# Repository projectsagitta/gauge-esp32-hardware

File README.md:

# sagitta-shield
Oceanographic measuring shield for TTGO T-Energy.

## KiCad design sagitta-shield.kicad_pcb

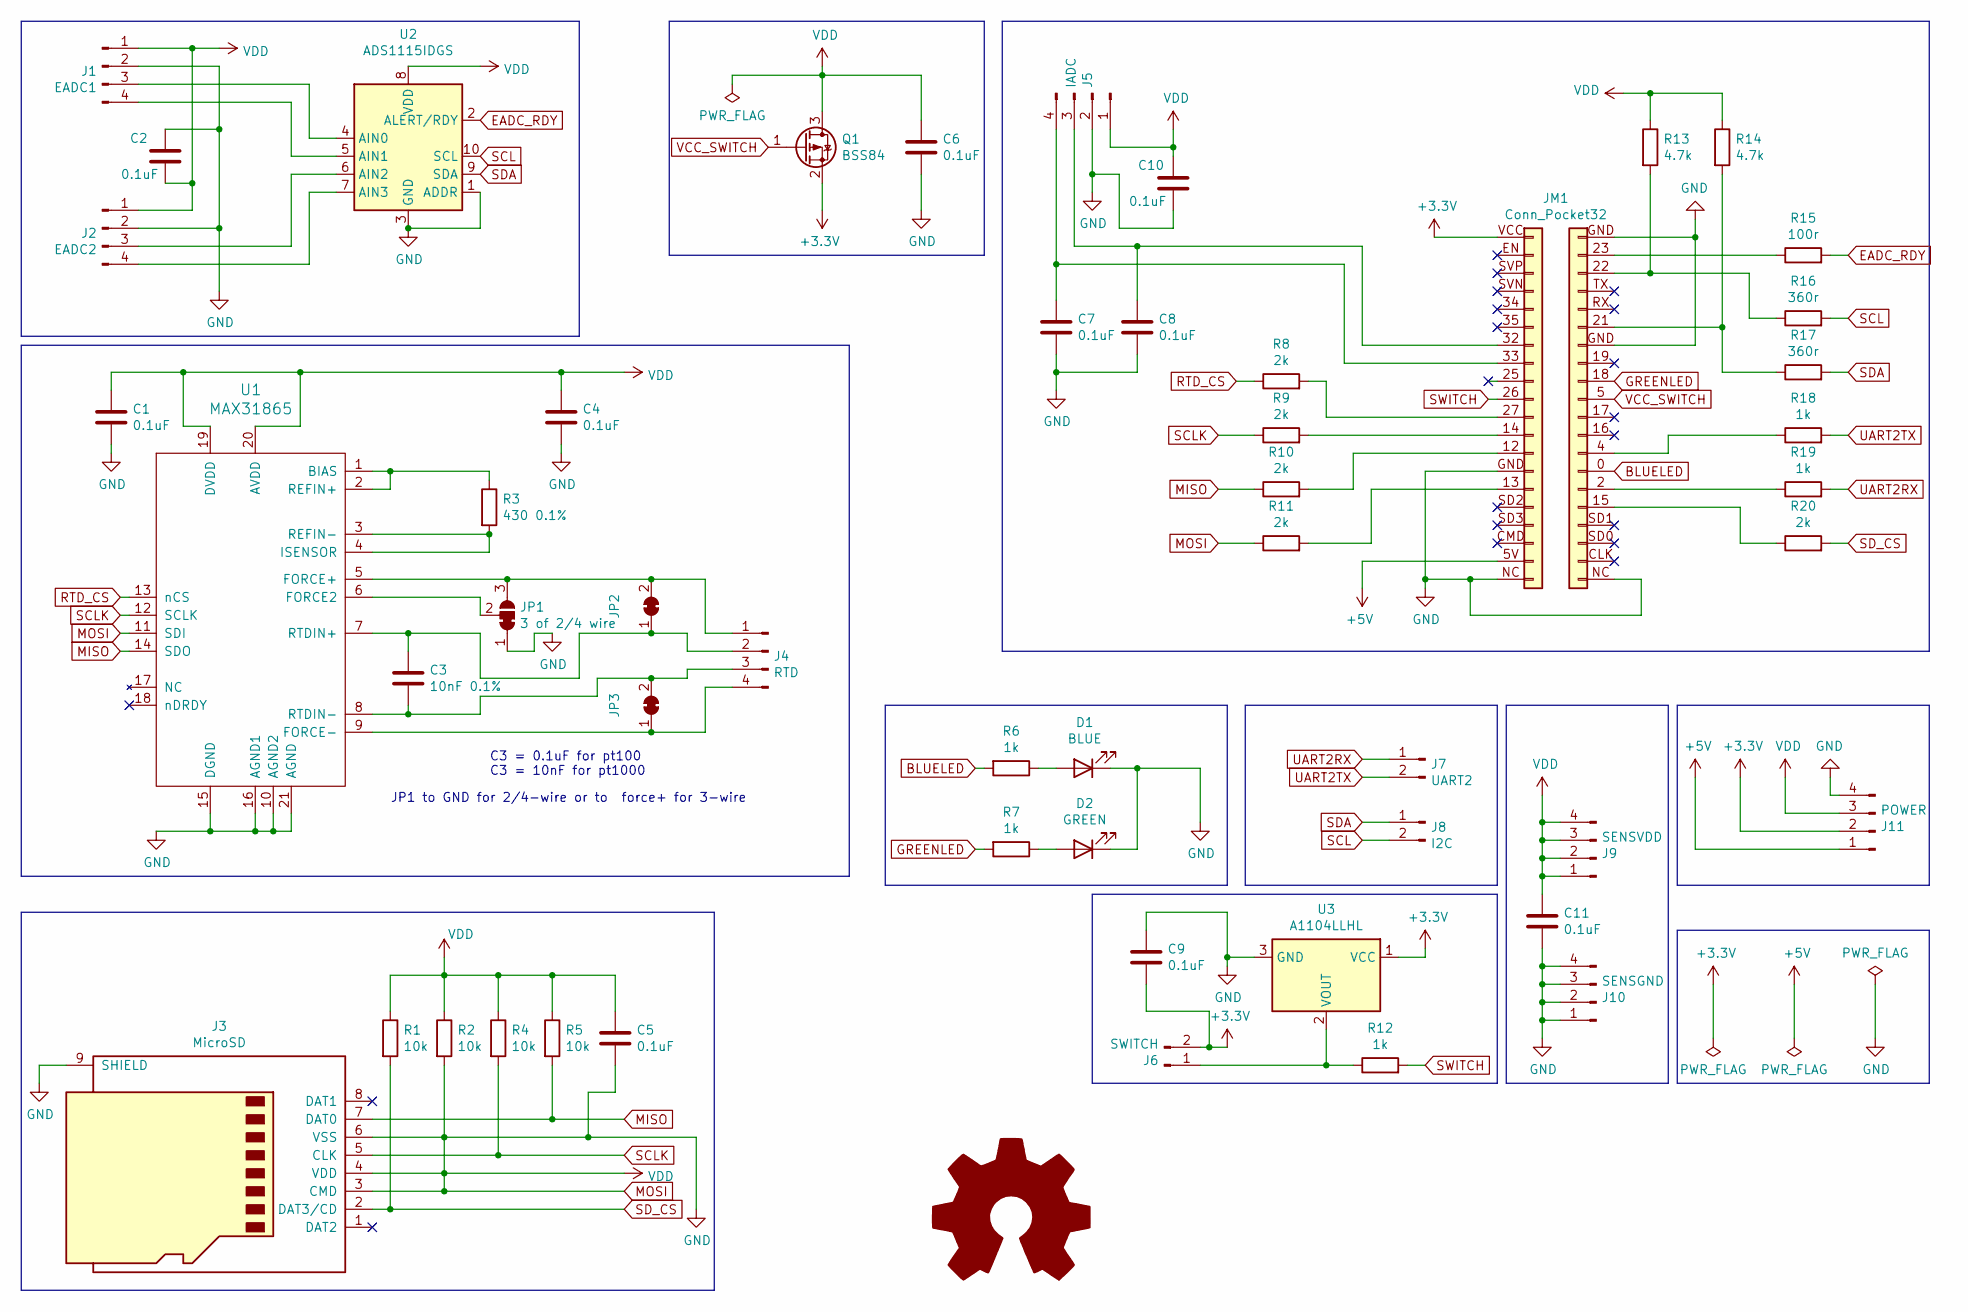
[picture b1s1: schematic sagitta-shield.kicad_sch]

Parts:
C1, C2, C4, C5, C6, C7, C8, C9, C10, C11: 0.1uF; C_0402_1005Metric_Pad0.74x0.62mm_HandSolder
C3: 10nF 0.1%; C_0603_1608Metric_Pad1.08x0.95mm_HandSolder
D1: BLUE; LED_0603_1608Metric_Pad1.05x0.95mm_HandSolder
D2: GREEN; LED_0603_1608Metric_Pad1.05x0.95mm_HandSolder
J1: EADC1; PinHeader_1x04_P2.54mm_Vertical
J2: EADC2; PinHeader_1x04_P2.54mm_Vertical
J3: MicroSD; microSD_HC_Hirose_DM3AT-SF-PEJM5
J4: RTD; PinHeader_1x04_P2.54mm_Vertical
J5: IADC; PinHeader_1x04_P2.54mm_Vertical
J6: SWITCH; PinSocket_1x02_P2.00mm_Vertical
J7: UART2; PinSocket_1x02_P2.00mm_Vertical
J8: I2C; PinSocket_1x02_P2.00mm_Vertical
J9: SENSVDD; PinSocket_1x04_P2.00mm_Vertical
J10: SENSGND; PinSocket_1x04_P2.00mm_Vertical
J11: POWER; PinSocket_1x04_P2.00mm_Vertical
JM1: Conn_Pocket32; Pocket32
JP1: 3 of 2/4 wire; SolderJumper-3_P1.3mm_Bridged12_RoundedPad1.0x1.5mm_NumberL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
JP2, JP3: SolderJumper-2_P1.3mm_Bridged_RoundedPad1.0x1.5mm
Q1: BSS84; SOT-23
R1, R2, R4, R5: 10k; R_0402_1005Metric_Pad0.72x0.64mm_HandSolder
R3: 430 0.1%; R_0603_1608Metric_Pad0.98x0.95mm_HandSolder
R6, R7, R12, R18, R19: 1k; R_0402_1005Metric_Pad0.72x0.64mm_HandSolder
R8, R9, R10, R11, R20: 2k; R_0402_1005Metric_Pad0.72x0.64mm_HandSolder
R13, R14: 4.7k; R_0402_1005Metric_Pad0.72x0.64mm_HandSolder
R15: 100r; R_0402_1005Metric_Pad0.72x0.64mm_HandSolder
R16, R17: 360r; R_0402_1005Metric_Pad0.72x0.64mm_HandSolder
U1: MAX31865; QFN-20-1EP_5x5mm_P0.65mm_EP3.35x3.35mm_ThermalVias
U2: ADS1115IDGS; TSSOP-10_3x3mm_P0.5mm
U3: A1104LLHL; SOT-23
openhardwarelogo1: Logo_Open_Hardware_Large; OSHW-Logo_5.7x6mm_SilkScreen

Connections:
+3V3: C9.1, J6.2, J11.2, JM1.VCC, Q1.2 (S), U3.1 (VCC)
+5V: J11.1, JM1.5V
BLUELED: JM1.0, R6.2
EADC_RDY: R15.2, U2.2 (ALERT/RDY)
GREENLED: JM1.18, R7.2
MISO: J3.7 (DAT0), R5.2, R10.1, U1.14 (SDO)
unnamed: C3.1, J4.2, JP2.1 (A), U1.7 (RTDIN+)
unnamed: C3.2, J4.3, JP3.2 (B), U1.8 (RTDIN-)
unnamed: C7.2, J5.4, JM1.33
unnamed: C8.2, J5.3, JM1.32
unnamed: D1.2 (A), R6.1
unnamed: D2.2 (A), R7.1
unnamed: J1.3, U2.4 (AIN0)
unnamed: J1.4, U2.5 (AIN1)
unnamed: J2.3, U2.6 (AIN2)
unnamed: J2.4, U2.7 (AIN3)
unnamed: J4.1, JP1.3 (B), JP2.2 (B), U1.5 (FORCE+)
unnamed: J4.4, JP3.1 (A), U1.9 (FORCE-)
unnamed: J6.1, R12.1, U3.2 (VOUT)
unnamed: JM1.2, R19.1
unnamed: JM1.4, R18.1
unnamed: JM1.12, R10.2
unnamed: JM1.13, R11.2
unnamed: JM1.14, R9.2
unnamed: JM1.15, R20.1
unnamed: JM1.21, R14.2, R17.1
unnamed: JM1.22, R13.2, R16.1
unnamed: JM1.23, R15.1
unnamed: JM1.27, R8.2
unnamed: JP1.2 (C), U1.6 (FORCE2)
unnamed: R3.1, U1.1 (BIAS), U1.2 (REFIN+)
unnamed: R3.2, U1.3 (REFIN-), U1.4 (ISENSOR)
RTD_CS: R8.1, U1.13 (nCS)
SCL: J8.2, R16.2, U2.10 (SCL)
SCLK: J3.5 (CLK), R4.2, R9.1, U1.12 (SCLK)
SDA: J8.1, R17.2, U2.9 (SDA)
SD_CS: J3.2 (DAT3/CD), R1.2, R20.2
SWITCH: JM1.26, R12.2
UART2RX: J7.1, R19.2
UART2TX: J7.2, R18.2
VCC_SWITCH: JM1.5, Q1.1 (G)

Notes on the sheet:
JP1 to GND for 2/4-wire or to force+ for 3-wire
C3 = 0.1uF for pt100 C3 = 10nF for pt1000

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
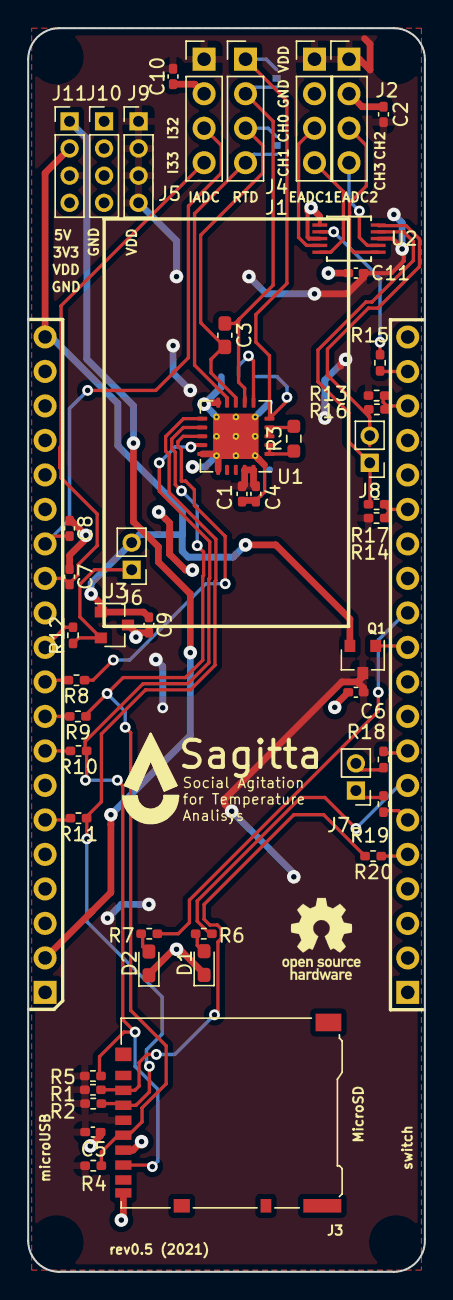
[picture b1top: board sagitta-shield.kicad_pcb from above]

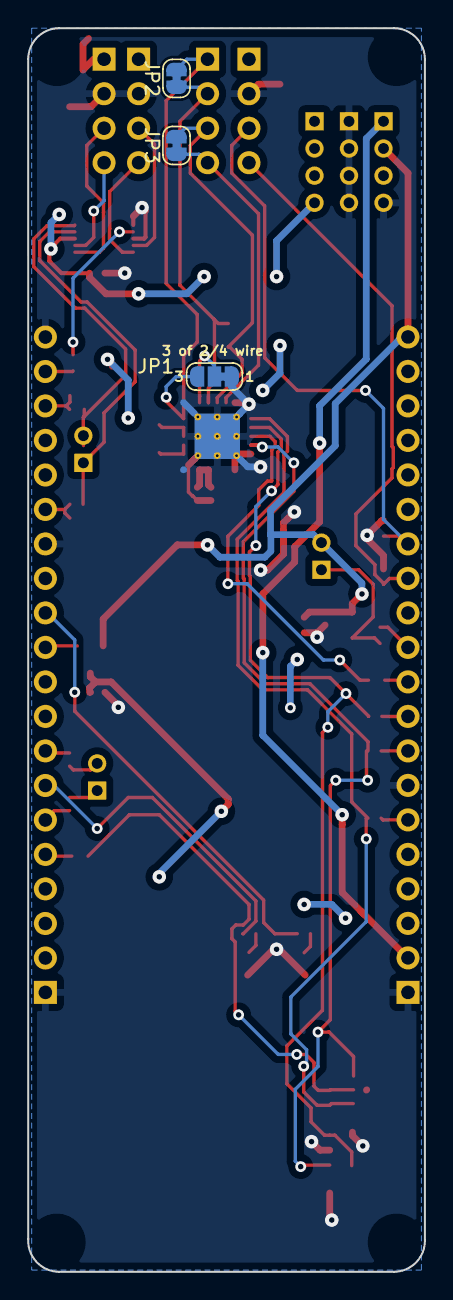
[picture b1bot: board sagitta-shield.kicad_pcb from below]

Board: 2 copper layers, 29.2 x 91.6 mm, 53 parts (3 on the bottom side), 44 nets.

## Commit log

2022-11-25 add design
2022-11-25 deleted trash
2023-04-03 fix previous version PCB's errors
